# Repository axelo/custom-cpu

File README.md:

# custom-cpu

A custom CPU built from 7400-series integrated circuits.

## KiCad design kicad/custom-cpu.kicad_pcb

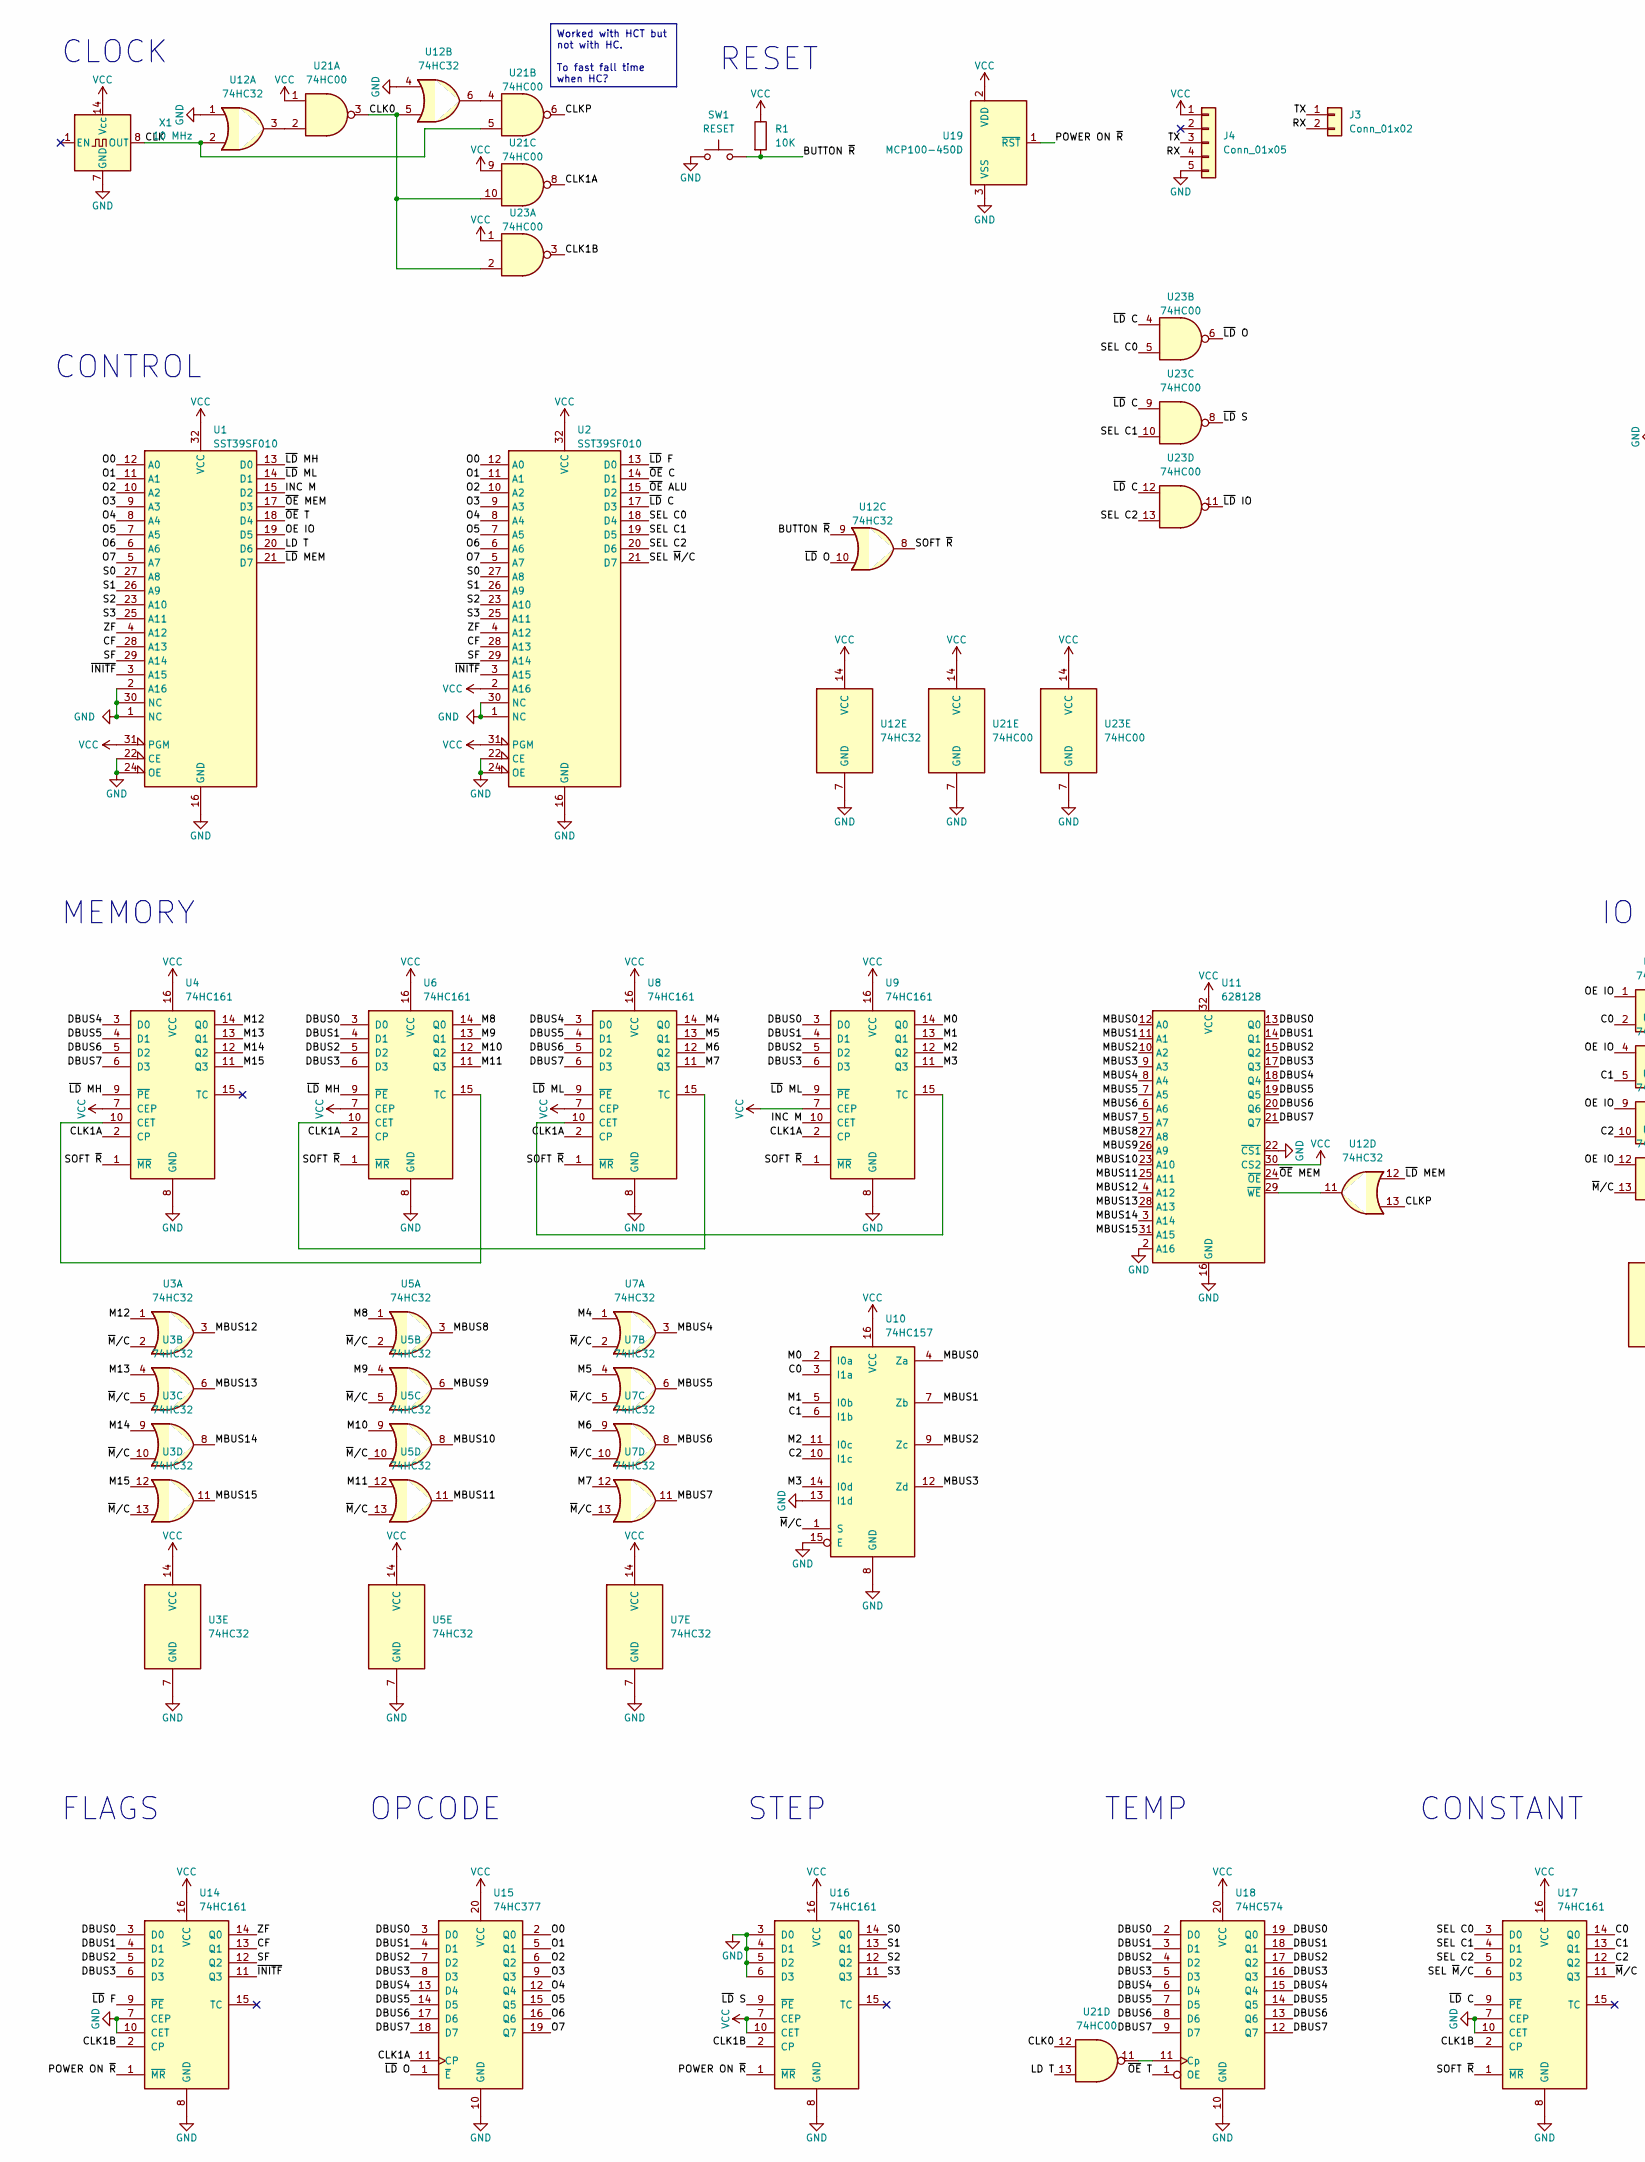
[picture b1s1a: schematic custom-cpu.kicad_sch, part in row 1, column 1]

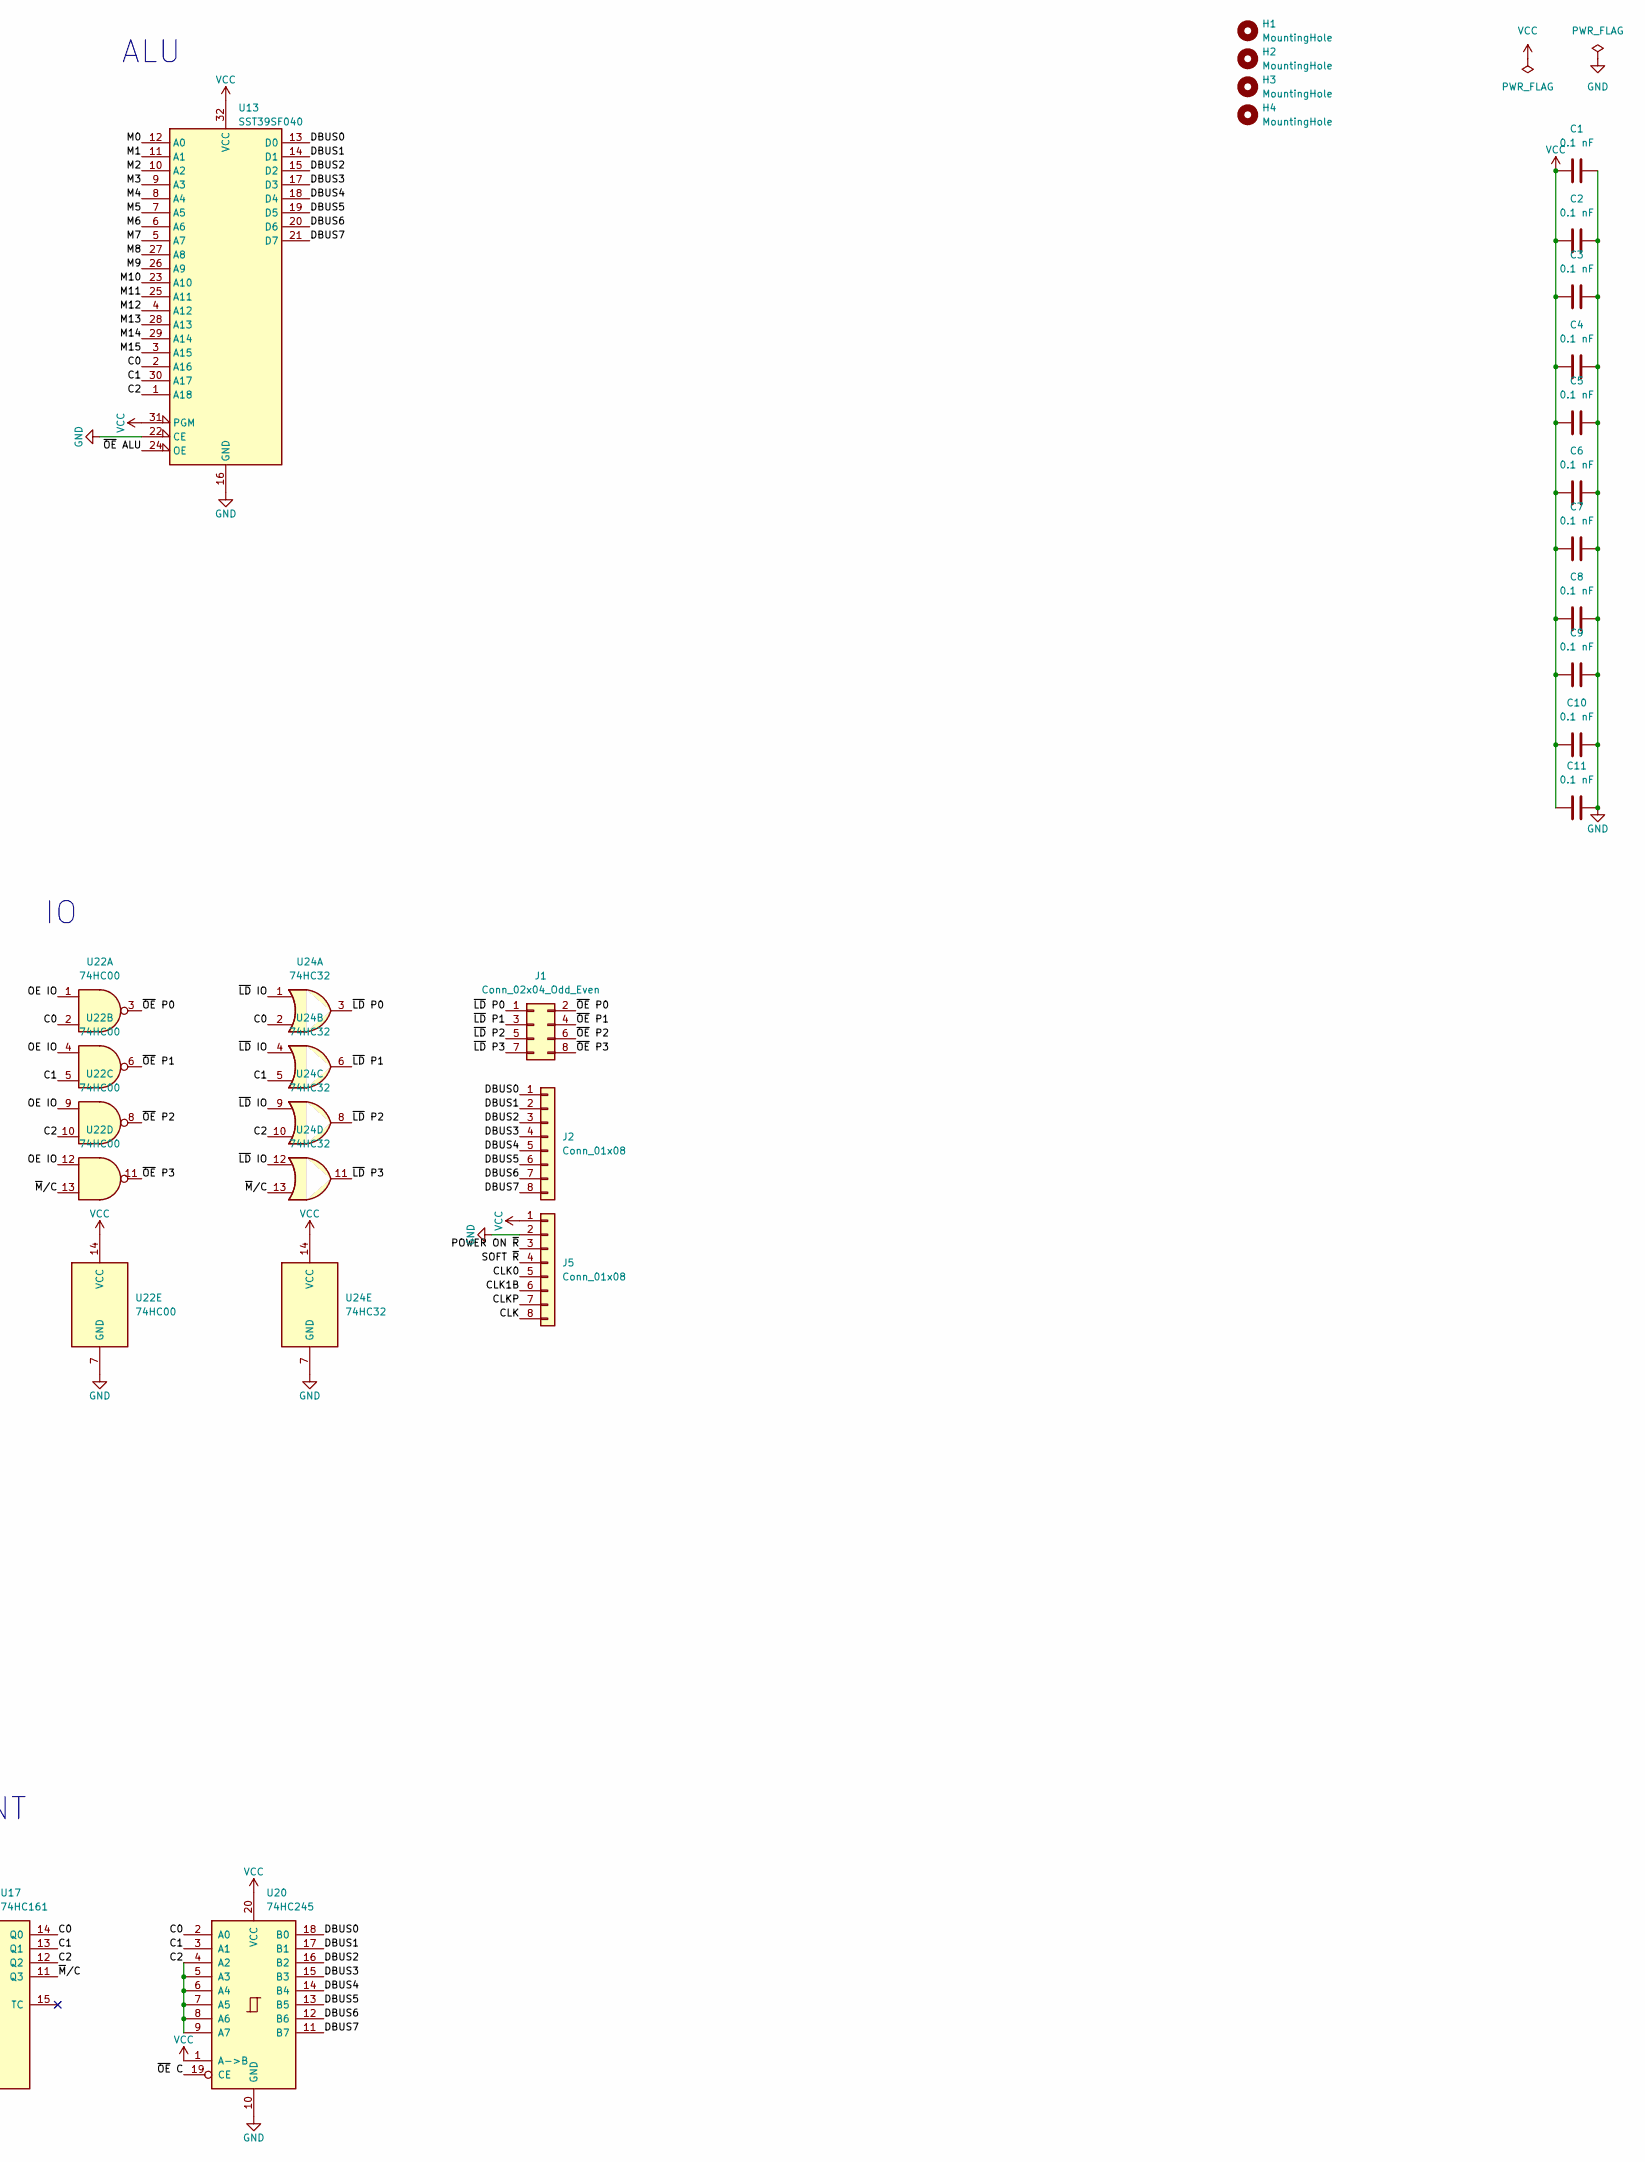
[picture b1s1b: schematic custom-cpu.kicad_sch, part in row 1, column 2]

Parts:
C1, C2, C3, C4, C5, C6, C7, C8, C9, C10, C11: 0.1 nF; C_Disc_D5.0mm_W2.5mm_P5.00mm
H1, H2, H3, H4: MountingHole; MountingHole_3.2mm_M3
J1: Conn_02x04_Odd_Even; PinSocket_2x04_P2.54mm_Vertical
J2, J5: Conn_01x08; PinSocket_1x08_P2.54mm_Vertical
J3: Conn_01x02; PinSocket_1x02_P2.54mm_Vertical
J4: Conn_01x05; PinSocket_1x05_P2.54mm_Vertical
R1: 10K; R_Axial_DIN0207_L6.3mm_D2.5mm_P7.62mm_Horizontal
SW1: RESET; SW_PUSH_6mm
U1, U2: SST39SF010; DIP-32_W15.24mm_Socket
U3, U5, U7, U12, U24: 74HC32; DIP-14_W7.62mm_Socket
U4, U6, U8, U9, U14, U16, U17: 74HC161; DIP-16_W7.62mm_Socket
U10: 74HC157; DIP-16_W7.62mm_Socket
U11: 628128; DIP-32_W15.24mm_Socket
U13: SST39SF040; DIP-32_W15.24mm_Socket
U15: 74HC377; DIP-20_W7.62mm_Socket
U18: 74HC574; DIP-20_W7.62mm_Socket
U19: MCP100-450D; PinHeader_1x03_P2.00mm_Vertical
U20: 74HC245; DIP-20_W7.62mm_Socket
U21, U22, U23: 74HC00; DIP-14_W7.62mm_Socket
X1: 10 MHz; Oscillator_DIP-14

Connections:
/BUTTON ~R: R1.2, SW1.2, U12.9
/C0: U10.3 (I1a), U13.2 (A16), U17.14 (Q0), U20.2 (A0), U22.2, U24.2
/C1: U10.6 (I1b), U13.30 (A17), U17.13 (Q1), U20.3 (A1), U22.5, U24.5
/C2: U10.10 (I1c), U13.1 (A18), U17.12 (Q2), U20.4 (A2), U20.5 (A3), U20.6 (A4), U20.7 (A5), U20.8 (A6), U20.9 (A7), U22.10, U24.10
/CF: U1.28 (A13), U2.28 (A13), U14.13 (Q1)
/CLK: J5.8, U12.2, U21.5, X1.8 (OUT)
/CLK0: J5.5, U12.5, U21.3, U21.10, U21.12, U23.2
/CLK1A: U4.2 (CP), U6.2 (CP), U8.2 (CP), U9.2 (CP), U15.11 (CP), U21.8
/CLK1B: J5.6, U14.2 (CP), U16.2 (CP), U17.2 (CP), U23.3
/CLKP: J5.7, U12.13, U21.6
/DBUS0: J2.1, U6.3 (D0), U9.3 (D0), U11.13 (Q0), U13.13 (D0), U14.3 (D0), U15.3 (D0), U18.2 (D0), U18.19 (Q0), U20.18 (B0)
/DBUS1: J2.2, U6.4 (D1), U9.4 (D1), U11.14 (Q1), U13.14 (D1), U14.4 (D1), U15.4 (D1), U18.3 (D1), U18.18 (Q1), U20.17 (B1)
/DBUS2: J2.3, U6.5 (D2), U9.5 (D2), U11.15 (Q2), U13.15 (D2), U14.5 (D2), U15.7 (D2), U18.4 (D2), U18.17 (Q2), U20.16 (B2)
/DBUS3: J2.4, U6.6 (D3), U9.6 (D3), U11.17 (Q3), U13.17 (D3), U14.6 (D3), U15.8 (D3), U18.5 (D3), U18.16 (Q3), U20.15 (B3)
/DBUS4: J2.5, U4.3 (D0), U8.3 (D0), U11.18 (Q4), U13.18 (D4), U15.13 (D4), U18.6 (D4), U18.15 (Q4), U20.14 (B4)
/DBUS5: J2.6, U4.4 (D1), U8.4 (D1), U11.19 (Q5), U13.19 (D5), U15.14 (D5), U18.7 (D5), U18.14 (Q5), U20.13 (B5)
/DBUS6: J2.7, U4.5 (D2), U8.5 (D2), U11.20 (Q6), U13.20 (D6), U15.17 (D6), U18.8 (D6), U18.13 (Q6), U20.12 (B6)
/DBUS7: J2.8, U4.6 (D3), U8.6 (D3), U11.21 (Q7), U13.21 (D7), U15.18 (D7), U18.9 (D7), U18.12 (Q7), U20.11 (B7)
/INC M: U1.15 (D2), U9.10 (CET)
/LD T: U1.20 (D6), U21.13
/M0: U9.14 (Q0), U10.2 (I0a), U13.12 (A0)
/M1: U9.13 (Q1), U10.5 (I0b), U13.11 (A1)
/M2: U9.12 (Q2), U10.11 (I0c), U13.10 (A2)
/M3: U9.11 (Q3), U10.14 (I0d), U13.9 (A3)
/M4: U7.1, U8.14 (Q0), U13.8 (A4)
/M5: U7.4, U8.13 (Q1), U13.7 (A5)
/M6: U7.9, U8.12 (Q2), U13.6 (A6)
/M7: U7.12, U8.11 (Q3), U13.5 (A7)
/M8: U5.1, U6.14 (Q0), U13.27 (A8)
/M9: U5.4, U6.13 (Q1), U13.26 (A9)
/M10: U5.9, U6.12 (Q2), U13.23 (A10)
/M11: U5.12, U6.11 (Q3), U13.25 (A11)
/M12: U3.1, U4.14 (Q0), U13.4 (A12)
/M13: U3.4, U4.13 (Q1), U13.28 (A13)
/M14: U3.9, U4.12 (Q2), U13.29 (A14)
/M15: U3.12, U4.11 (Q3), U13.3 (A15)
/MBUS0: U10.4 (Za), U11.12 (A0)
/MBUS1: U10.7 (Zb), U11.11 (A1)
/MBUS2: U10.9 (Zc), U11.10 (A2)
/MBUS3: U10.12 (Zd), U11.9 (A3)
/MBUS4: U7.3, U11.8 (A4)
/MBUS5: U7.6, U11.7 (A5)
/MBUS6: U7.8, U11.6 (A6)
/MBUS7: U7.11, U11.5 (A7)
/MBUS8: U5.3, U11.27 (A8)
/MBUS9: U5.6, U11.26 (A9)
/MBUS10: U5.8, U11.23 (A10)
/MBUS11: U5.11, U11.25 (A11)
/MBUS12: U3.3, U11.4 (A12)
/MBUS13: U3.6, U11.28 (A13)
/MBUS14: U3.8, U11.3 (A14)
/MBUS15: U3.11, U11.31 (A15)
/O0: U1.12 (A0), U2.12 (A0), U15.2 (Q0)
/O1: U1.11 (A1), U2.11 (A1), U15.5 (Q1)
/O2: U1.10 (A2), U2.10 (A2), U15.6 (Q2)
/O3: U1.9 (A3), U2.9 (A3), U15.9 (Q3)
/O4: U1.8 (A4), U2.8 (A4), U15.12 (Q4)
/O5: U1.7 (A5), U2.7 (A5), U15.15 (Q5)
/O6: U1.6 (A6), U2.6 (A6), U15.16 (Q6)
/O7: U1.5 (A7), U2.5 (A7), U15.19 (Q7)
/OE IO: U1.19 (D5), U22.1, U22.4, U22.9, U22.12
/POWER ON ~R: J5.3, U14.1 (~MR), U16.1 (~MR), U19.1 (~RST)
/RX: J3.2, J4.4
/S0: U1.27 (A8), U2.27 (A8), U16.14 (Q0)
/S1: U1.26 (A9), U2.26 (A9), U16.13 (Q1)
/S2: U1.23 (A10), U2.23 (A10), U16.12 (Q2)
/S3: U1.25 (A11), U2.25 (A11), U16.11 (Q3)
/SEL C0: U2.18 (D4), U17.3 (D0), U23.5
/SEL C1: U2.19 (D5), U17.4 (D1), U23.10
/SEL C2: U2.20 (D6), U17.5 (D2), U23.13
/SEL ~M/C: U2.21 (D7), U17.6 (D3)
/SF: U1.29 (A14), U2.29 (A14), U14.12 (Q2)
/SOFT ~R: J5.4, U4.1 (~MR), U6.1 (~MR), U8.1 (~MR), U9.1 (~MR), U12.8, U17.1 (~MR)
/TX: J3.1, J4.3
/ZF: U1.4 (A12), U2.4 (A12), U14.14 (Q0)
/~INITF: U1.3 (A15), U2.3 (A15), U14.11 (Q3)
/~LD C: U2.17 (D3), U17.9 (~PE), U23.4, U23.9, U23.12
/~LD F: U2.13 (D0), U14.9 (~PE)
/~LD IO: U23.11, U24.1, U24.4, U24.9, U24.12
/~LD MEM: U1.21 (D7), U12.12
/~LD MH: U1.13 (D0), U4.9 (~PE), U6.9 (~PE)
/~LD ML: U1.14 (D1), U8.9 (~PE), U9.9 (~PE)
/~LD O: U12.10, U15.1 (~E), U23.6
/~LD P0: J1.1, U24.3
/~LD P1: J1.3, U24.6
/~LD P2: J1.5, U24.8
/~LD P3: J1.7, U24.11
/~LD S: U16.9 (~PE), U23.8
/~M/C: U3.2, U3.5, U3.10, U3.13, U5.2, U5.5, U5.10, U5.13, U7.2, U7.5, U7.10, U7.13, U10.1 (S), U17.11 (Q3), U22.13, U24.13
/~OE ALU: U2.15 (D2), U13.24 (OE)
/~OE C: U2.14 (D1), U20.19 (CE)
/~OE MEM: U1.17 (D3), U11.24 (~OE)
/~OE P0: J1.2, U22.3
/~OE P1: J1.4, U22.6
/~OE P2: J1.6, U22.8
/~OE P3: J1.8, U22.11
/~OE T: U1.18 (D4), U18.1 (OE)
GND: C1.2, C2.2, C3.2, C4.2, C5.2, C6.2, C7.2, C8.2, C9.2, C10.2, C11.2, J4.5, J5.2, SW1.1, U1.1 (NC), U1.2 (A16), U1.16 (GND), U1.22 (CE), U1.24 (OE), U1.30 (NC), U2.1 (NC), U2.16 (GND), U2.22 (CE), U2.24 (OE), U2.30 (NC), U3.7 (GND), U4.8 (GND), U5.7 (GND), U6.8 (GND), U7.7 (GND), U8.8 (GND), U9.8 (GND), U10.8 (GND), U10.13 (I1d), U10.15 (E), U11.2 (A16), U11.16 (GND), U11.22 (~CS1), U12.1, U12.4, U12.7 (GND), U13.16 (GND), U13.22 (CE), U14.7 (CEP), U14.8 (GND), U14.10 (CET), U15.10 (GND), U16.3 (D0), U16.4 (D1), U16.5 (D2), U16.6 (D3), U16.8 (GND), U17.7 (CEP), U17.8 (GND), U17.10 (CET), U18.10 (GND), U19.3 (VSS), U20.10 (GND), U21.7 (GND), U22.7 (GND), U23.7 (GND), U24.7 (GND), X1.7 (GND)
unnamed: U4.10 (CET), U6.15 (TC)
unnamed: U6.10 (CET), U8.15 (TC)
unnamed: U8.10 (CET), U9.15 (TC)
unnamed: U11.29 (~WE), U12.11
unnamed: U12.3, U21.2
unnamed: U12.6, U21.4
unnamed: U18.11 (Cp), U21.11
VCC: C1.1, C2.1, C3.1, C4.1, C5.1, C6.1, C7.1, C8.1, C9.1, C10.1, C11.1, J4.1, J5.1, R1.1, U1.31 (PGM), U1.32 (VCC), U2.2 (A16), U2.31 (PGM), U2.32 (VCC), U3.14 (VCC), U4.7 (CEP), U4.16 (VCC), U5.14 (VCC), U6.7 (CEP), U6.16 (VCC), U7.14 (VCC), U8.7 (CEP), U8.16 (VCC), U9.7 (CEP), U9.16 (VCC), U10.16 (VCC), U11.30 (CS2), U11.32 (VCC), U12.14 (VCC), U13.31 (PGM), U13.32 (VCC), U14.16 (VCC), U15.20 (VCC), U16.7 (CEP), U16.10 (CET), U16.16 (VCC), U17.16 (VCC), U18.20 (VCC), U19.2 (VDD), U20.1 (A->B), U20.20 (VCC), U21.1, U21.9, U21.14 (VCC), U22.14 (VCC), U23.1, U23.14 (VCC), U24.14 (VCC), X1.14 (Vcc)

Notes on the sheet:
Worked with HCT but not with HC. To fast fall time when HC?
CONTROL
FLAGS
RESET
CONSTANT
OPCODE
CLOCK
STEP
ALU
MEMORY
TEMP

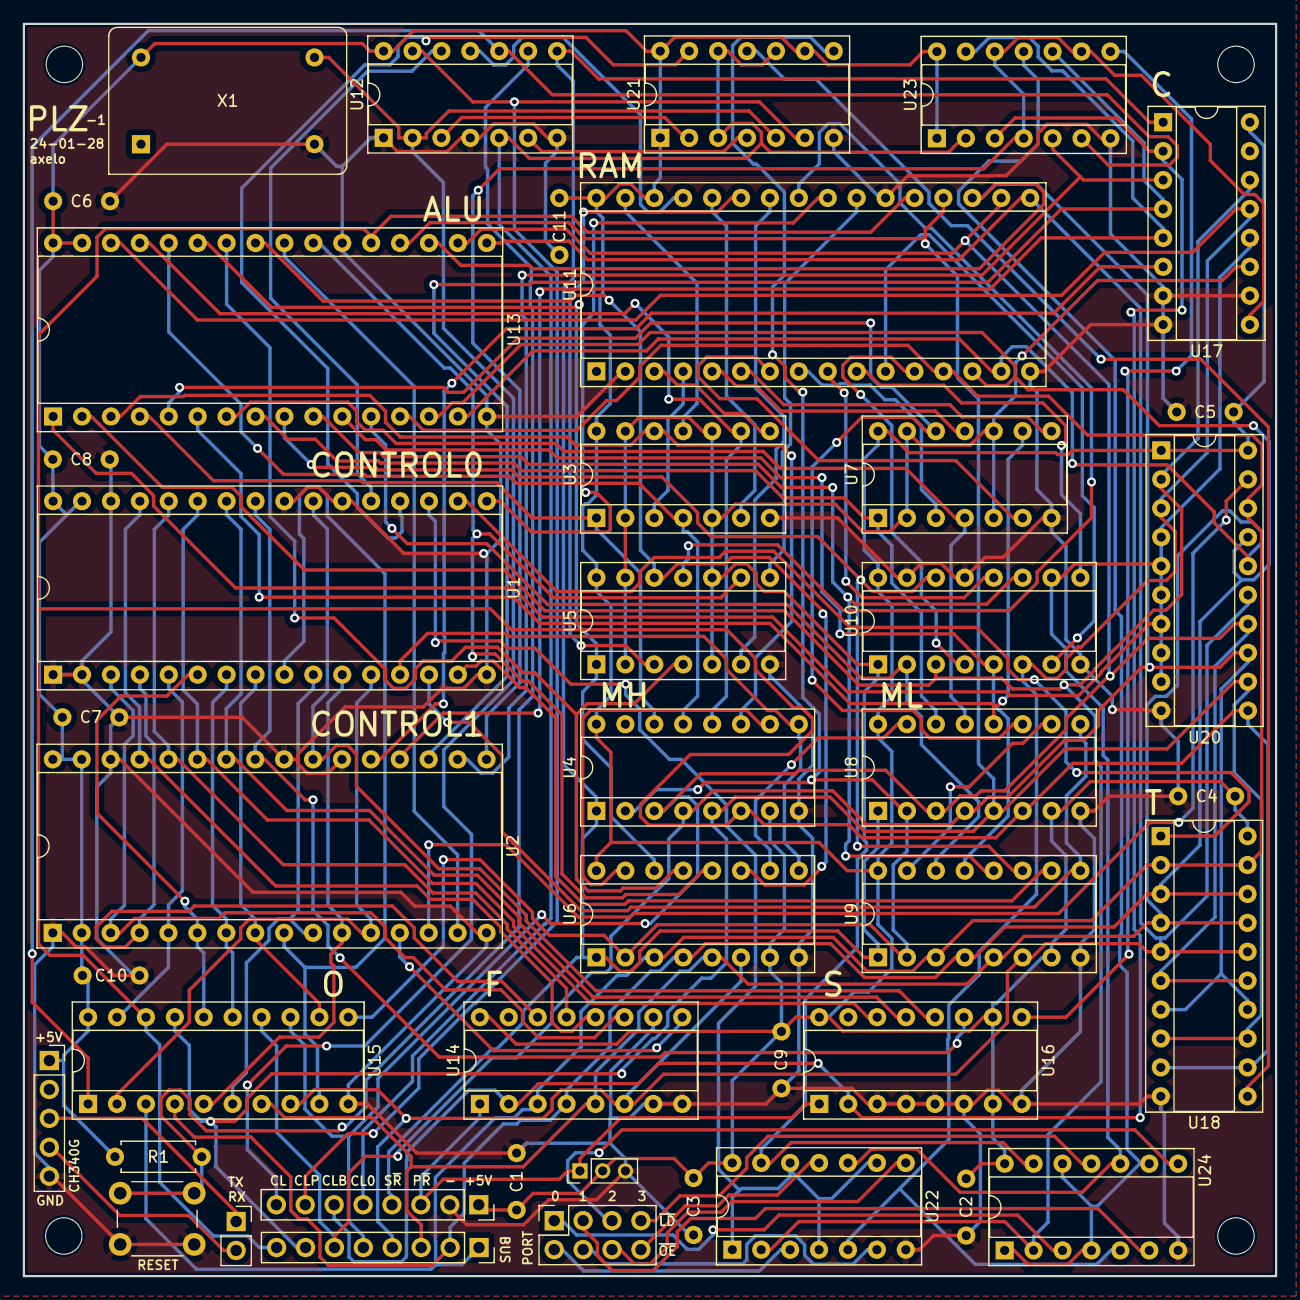
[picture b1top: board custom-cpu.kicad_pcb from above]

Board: 2 copper layers, 110.0 x 110.0 mm, 47 parts (0 on the bottom side), 106 nets.

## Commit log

2024-03-03 Source
2024-03-03 Add schematics
2024-03-03 .gitignore
2024-03-03 PLZ-1 (#1)
2024-03-18 non blocking uart read
2024-03-18 non blocking uart read (#2)
2024-03-30 Initial test setup
2024-03-30 Initial test setup (#3)
2024-03-31 emulator
2024-03-31 emulator (#4)
2024-04-06 u8 dec string conversion
2024-04-06 u8 decimal string conversion (#5)
2024-05-01 More opcodes
2024-05-01 Prefix all with O_
2024-05-01 More opcodes (#6)
2024-05-01 Minor code clean up
2024-05-01 Minor code clean up (#7)
2024-09-21 more tests
2024-09-24 initial add i8
2024-09-25 addc
2024-09-28 shl shr test reset
2024-09-30 jz jnz jc jnc
2024-09-30 jmp k, jal k
2024-10-01 push pop
2024-10-01 rename opcode to instruction
2024-10-01 ld [i++], a
2024-10-01 replace opcode with instruction
2024-10-02 replace strlen with pointer
2024-10-04 subc
2024-10-06 and, out, uart
2024-10-15 reset fix. spi2
2024-10-19 example boot rom for verifying ram writes
2024-10-23 I no longer needs reset. Compressed instructions setup
2024-10-26 simplify
2024-11-10 UART simulation
2024-11-14 uart
2024-11-23 small fixes
2024-11-23 dec jcmpz
2025-01-07 rx rts
2025-01-12 91136
2025-01-12 182272
2025-01-14 364544
2025-01-30 Simulate UART in Digital
